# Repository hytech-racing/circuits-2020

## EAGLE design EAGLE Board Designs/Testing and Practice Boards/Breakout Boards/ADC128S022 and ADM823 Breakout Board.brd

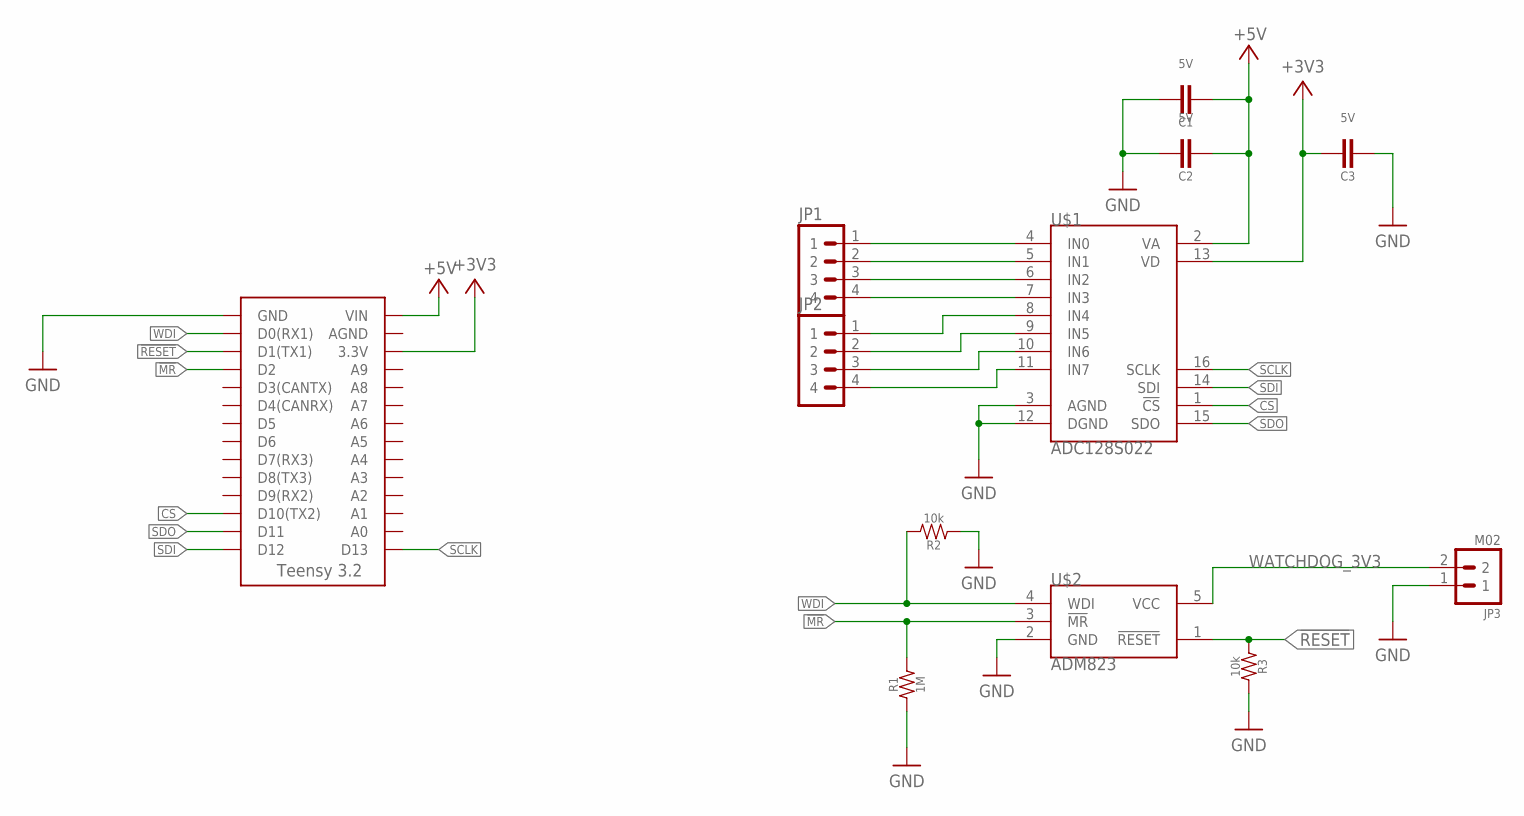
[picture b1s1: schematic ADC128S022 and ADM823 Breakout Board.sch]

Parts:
C1: 1uF; 0603-CAP
C2, C3: 0.1uF; 0603-CAP
JP1, JP2: M04; 1X04
JP3: M02; 1X02
R1: 1M; 0603-RES
R2, R3: 10k; 0603-RES
U$1: ADC128S022; TSSOP-16
U$2: ADM823; SOT323-5
U$3: TEENSY_3.2_SIMPLE

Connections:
!MR!: R1.2, U$2.3 (!MR!), U$3.D2
!RESET!: R3.1, U$2.1 (!RESET!), U$3.D1(TX1)
+3V3: C3.1, U$1.13 (VD), U$3.3.3V
+5V: C1.2, C2.2, U$1.2 (VA), U$3.VIN
CS: U$1.1 (!CS!), U$3.D10(TX2)
GND: C1.1, C2.1, C3.2, JP3.1, R1.1, R2.1, R3.2, U$1.3 (AGND), U$1.12 (DGND), U$2.2 (GND), U$3.GND
unnamed: JP1.1, U$1.4 (IN0)
unnamed: JP1.2, U$1.5 (IN1)
unnamed: JP1.3, U$1.6 (IN2)
unnamed: JP1.4, U$1.7 (IN3)
unnamed: JP2.1, U$1.8 (IN4)
unnamed: JP2.2, U$1.9 (IN5)
unnamed: JP2.3, U$1.10 (IN6)
unnamed: JP2.4, U$1.11 (IN7)
SCLK: U$1.16 (SCLK), U$3.D13
SDI: U$1.14 (SDI), U$3.D12
SDO: U$1.15 (SDO), U$3.D11
WATCHDOG_3V3: JP3.2, U$2.5 (VCC)
WDI: R2.2, U$2.4 (WDI), U$3.D0(RX1)

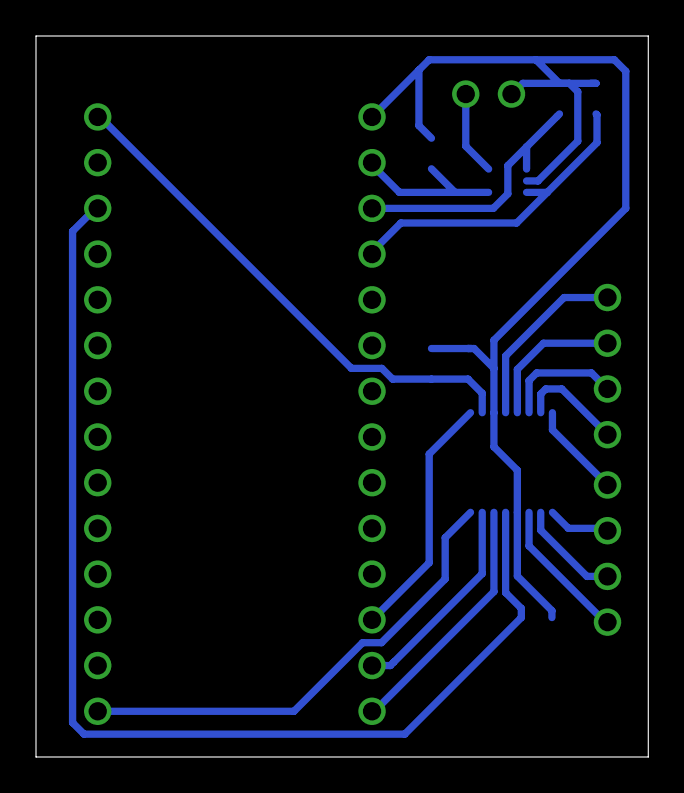
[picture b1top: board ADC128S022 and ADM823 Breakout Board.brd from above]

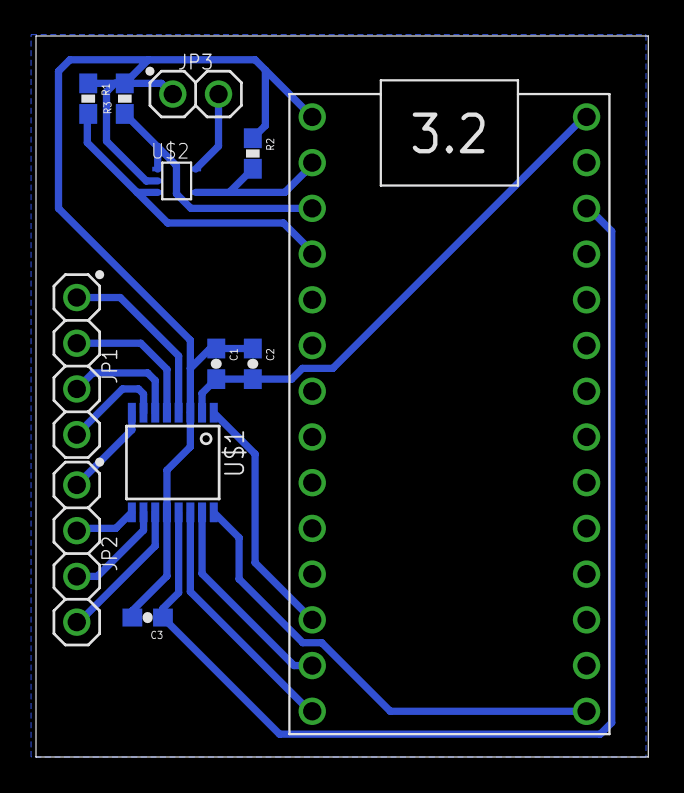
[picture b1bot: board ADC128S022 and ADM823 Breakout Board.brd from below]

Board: 1 copper layer, 34.0 x 40.1 mm, 12 parts (12 on the bottom side), 19 nets.

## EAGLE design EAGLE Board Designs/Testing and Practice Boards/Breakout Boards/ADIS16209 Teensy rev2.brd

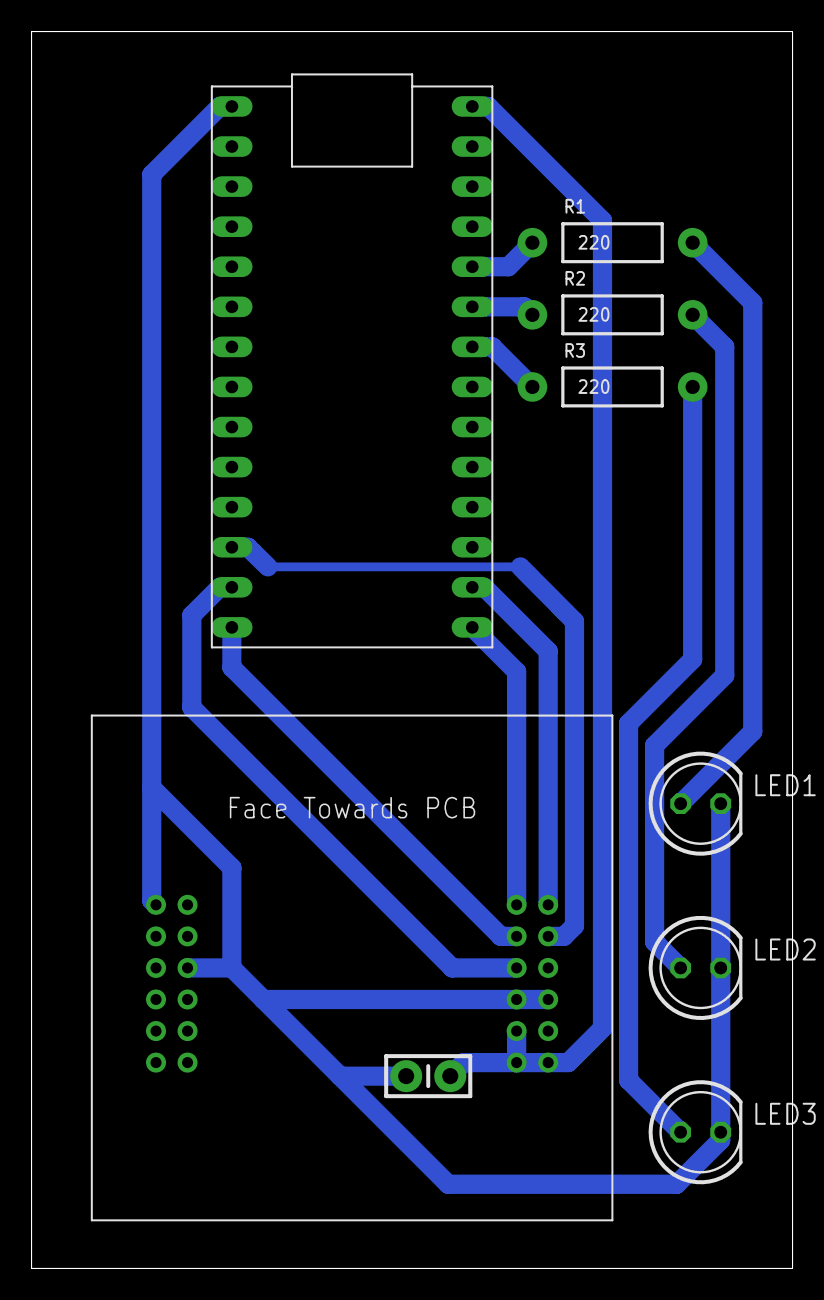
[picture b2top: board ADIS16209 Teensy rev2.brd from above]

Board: 2 copper layers, 48.2 x 78.4 mm, 9 parts (0 on the bottom side), 13 nets.

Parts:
C1: 1uF; CAP-PTH-SMALL-KIT
LED1, LED2, LED3: LED-5MM
R1, R2, R3: 220; AXIAL-0.4
U$1: ADIS16209/PCB
U$2: TEENSY_3.2_SIMPLE

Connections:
+3V3: C1.2, U$1.P$10, U$1.P$11, U$1.P$12, U$2.VIN
CS: U$1.P$3, U$2.D10(TX2)
GND: C1.1, LED1.K, LED2.K, LED3.K, U$1.P$7, U$1.P$8, U$1.P$14, U$1.P$17, U$2.GND
MISO: U$1.P$4, U$2.D12
MOSI: U$1.P$6, U$2.D11
unnamed: LED1.A, R1.P$2
unnamed: U$1.P$1, U$2.A0
unnamed: R1.P$1, U$2.A8
unnamed: R2.P$1, U$2.A7
unnamed: R3.P$1, U$2.A6
unnamed: LED2.A, R2.P$2
unnamed: LED3.A, R3.P$2
SCK: U$1.P$2, U$2.D13

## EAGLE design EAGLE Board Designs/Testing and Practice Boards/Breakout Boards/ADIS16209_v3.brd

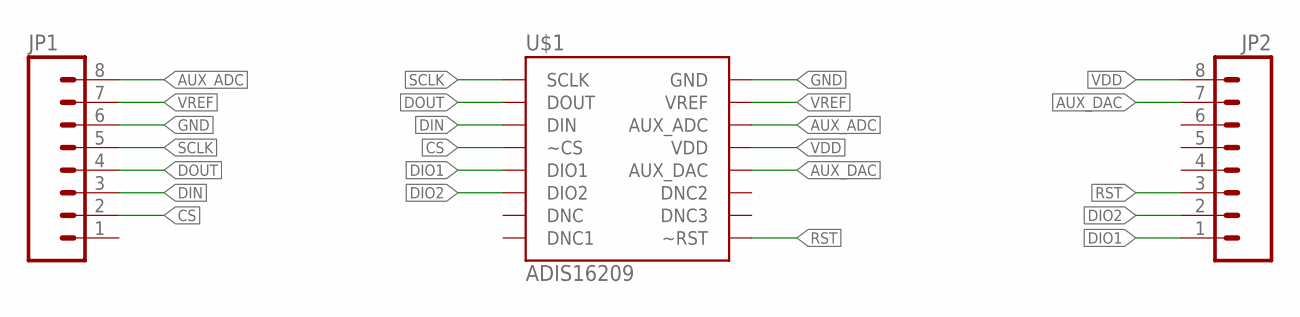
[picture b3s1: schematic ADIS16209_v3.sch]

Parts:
JP1, JP2: M08; 1X08
U$1: ADIS16209; CC-16-2

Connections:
AUX_ADC: JP1.8, U$1.P$14 (AUX_ADC)
AUX_DAC: JP2.7, U$1.P$12 (AUX_DAC)
CS: JP1.2, U$1.P$4 (~CS)
DIN: JP1.3, U$1.P$3 (DIN)
DIO1: JP2.1, U$1.P$5 (DIO1)
DIO2: JP2.2, U$1.P$6 (DIO2)
DOUT: JP1.4, U$1.P$2 (DOUT)
GND: JP1.6, U$1.P$16 (GND)
RST: JP2.3, U$1.P$9 (~RST)
SCLK: JP1.5, U$1.P$1 (SCLK)
VDD: JP2.8, U$1.P$13 (VDD)
VREF: JP1.7, U$1.P$15 (VREF)

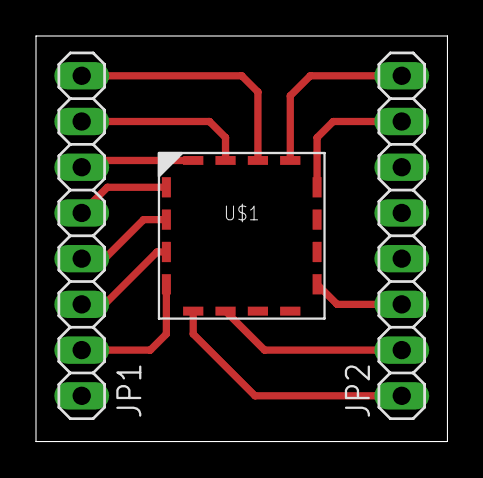
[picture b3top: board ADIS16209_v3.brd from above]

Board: 2 copper layers, 22.9 x 22.5 mm, 3 parts (0 on the bottom side), 12 nets.

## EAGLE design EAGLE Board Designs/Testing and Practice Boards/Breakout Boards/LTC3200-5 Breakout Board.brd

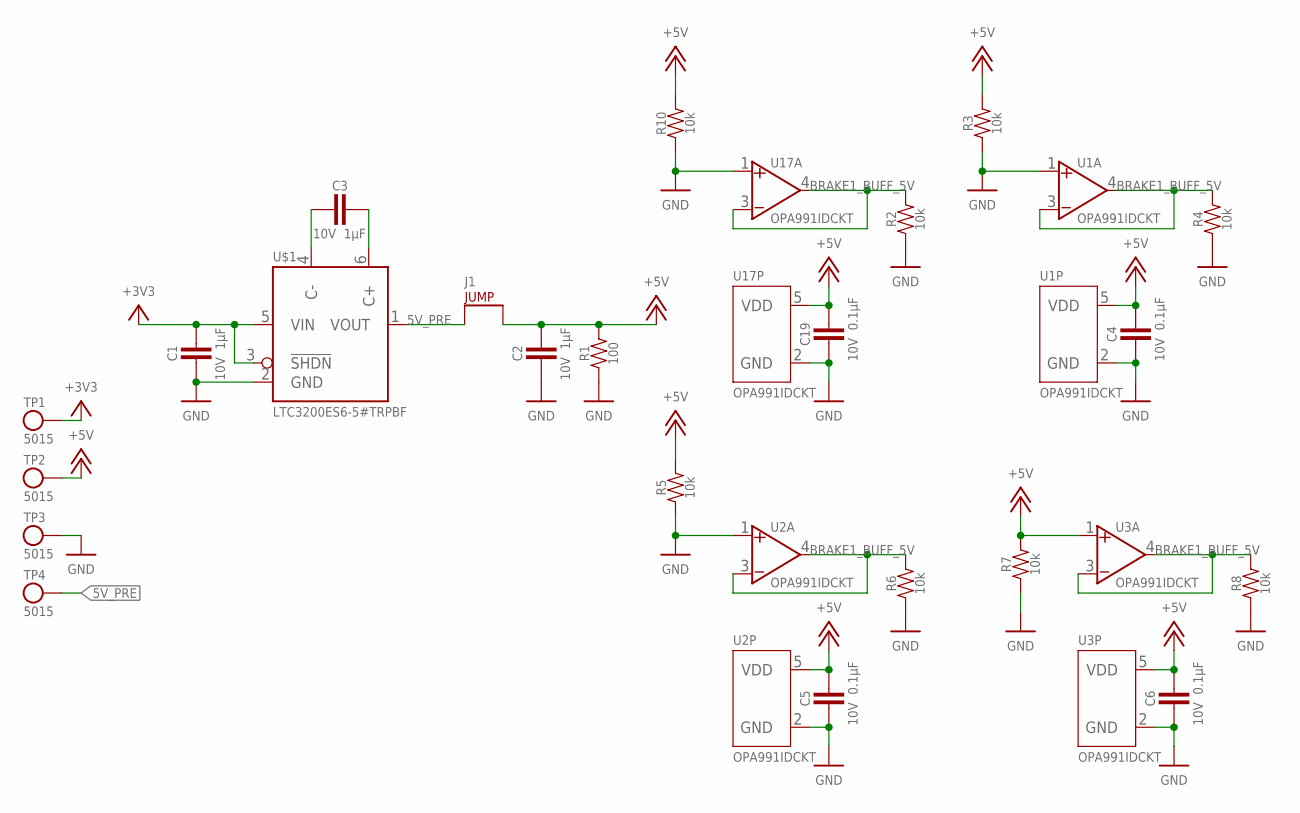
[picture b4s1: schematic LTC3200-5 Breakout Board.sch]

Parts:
C1, C2, C3: CAPACITOR_0603_10V_1UF; 0603-CAP
C4, C5, C6, C19: CAPACITOR_0603_10V_0.1UF; 0603-CAP
J1: JUMPER_1X02_; 1X02
R1: RESISTOR_0603_100; 0603-RES
R2, R3, R4, R5, R6, R7, R8, R10: RESISTOR_0603_10K; 0603-RES
TP1, TP2, TP3, TP4: TEST_POINT; MICRO_MINIATURE
U1, U2, U3, U17: OPAMP_1_CHANNEL_OPA991; SC-70-5
U$1: LTC3200-5; SOT-23-6

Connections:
5V_PRE: J1.1, TP4.1, U$1.1 (VOUT)
+3V3: C1.1, TP1.1, U$1.3 (!SHDN), U$1.5 (VIN)
+5V: C2.1, C4.1, C5.1, C6.1, C19.1, J1.2, R1.2, R3.2, R5.2, R7.2, R10.2, TP2.1, U1.5 (VDD), U2.5 (VDD), U3.1 (VIN+), U3.5 (VDD), U17.5 (VDD)
BRAKE1_BUFF_5V: R2.2, R4.2, R6.2, R8.2, U1.3 (VIN-), U1.4 (VOUT), U2.3 (VIN-), U2.4 (VOUT), U3.3 (VIN-), U3.4 (VOUT), U17.3 (VIN-), U17.4 (VOUT)
GND: C1.2, C2.2, C4.2, C5.2, C6.2, C19.2, R1.1, R2.1, R3.1, R4.1, R5.1, R6.1, R7.1, R8.1, R10.1, TP3.1, U1.1 (VIN+), U1.2 (GND), U2.1 (VIN+), U2.2 (GND), U3.2 (GND), U17.1 (VIN+), U17.2 (GND), U$1.2 (GND)
unnamed: C3.2, U$1.4 (C-)
unnamed: C3.1, U$1.6 (C+)

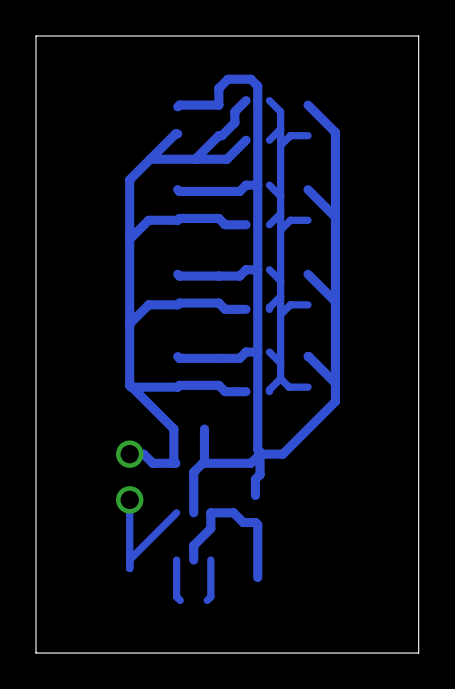
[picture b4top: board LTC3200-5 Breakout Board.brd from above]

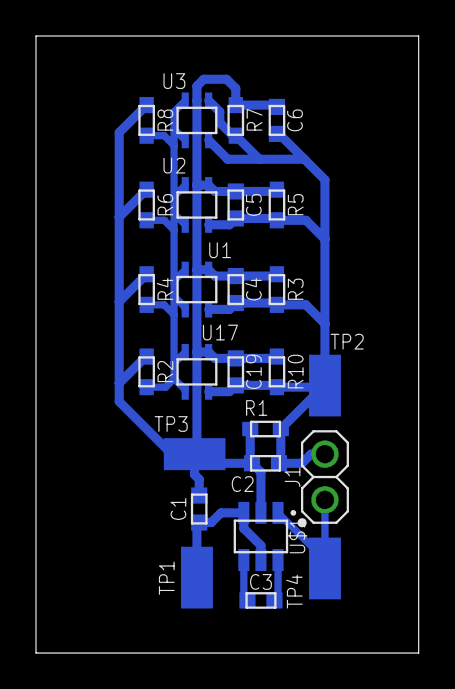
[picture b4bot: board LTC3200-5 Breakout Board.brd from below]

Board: 1 copper layer, 21.3 x 34.3 mm, 26 parts (26 on the bottom side), 7 nets.

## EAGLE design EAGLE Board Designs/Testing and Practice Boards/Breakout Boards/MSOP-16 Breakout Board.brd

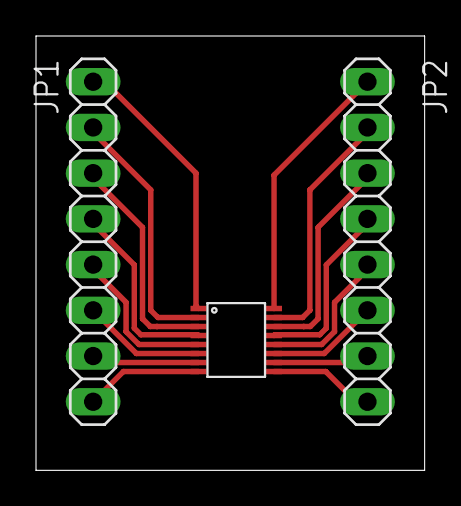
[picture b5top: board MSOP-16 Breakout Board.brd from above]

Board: 2 copper layers, 21.6 x 24.1 mm, 3 parts (0 on the bottom side), 15 nets.

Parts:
JP1, JP2: 1X08
U$1: LTC6820; MSOP-16

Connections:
unnamed: JP1.8, U$1.8
unnamed: JP1.6, U$1.6
unnamed: JP1.5, U$1.5
unnamed: JP1.4, U$1.4
unnamed: JP1.3, U$1.3
unnamed: JP1.1, U$1.1
unnamed: JP1.2, JP1.7, U$1.2, U$1.7
unnamed: JP2.8, U$1.9
unnamed: JP2.7, U$1.10
unnamed: JP2.6, U$1.11
unnamed: JP2.5, U$1.12
unnamed: JP2.4, U$1.13
unnamed: JP2.3, U$1.14
unnamed: JP2.2, U$1.15
unnamed: JP2.1, U$1.16

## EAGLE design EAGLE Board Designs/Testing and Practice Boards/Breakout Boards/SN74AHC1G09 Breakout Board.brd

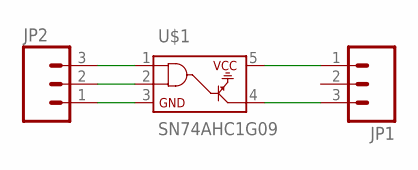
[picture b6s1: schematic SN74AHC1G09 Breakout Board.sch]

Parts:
JP1, JP2: M03; 1X03
U$1: SN74AHC1G09; SOT-23-5

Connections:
unnamed: JP2.3, U$1.1
unnamed: JP2.2, U$1.2
unnamed: JP2.1, U$1.3
unnamed: JP1.1, U$1.5
unnamed: JP1.3, U$1.4

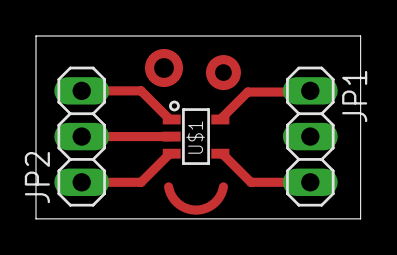
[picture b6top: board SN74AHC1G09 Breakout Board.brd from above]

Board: 2 copper layers, 18.0 x 10.2 mm, 3 parts (0 on the bottom side), 5 nets.

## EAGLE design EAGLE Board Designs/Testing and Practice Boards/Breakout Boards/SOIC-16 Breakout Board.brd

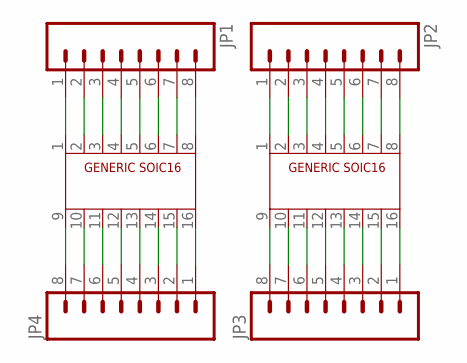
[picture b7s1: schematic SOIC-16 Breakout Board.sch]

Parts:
JP1, JP2, JP3, JP4: M08; 1X08
U$1, U$2: SOIC16; SOIC-16

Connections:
unnamed: JP1.1, U$1.1
unnamed: JP1.2, U$1.2
unnamed: JP1.3, U$1.3
unnamed: JP1.4, U$1.4
unnamed: JP1.5, U$1.5
unnamed: JP1.6, U$1.6
unnamed: JP1.7, U$1.7
unnamed: JP1.8, U$1.8
unnamed: JP2.1, U$2.1
unnamed: JP2.2, U$2.2
unnamed: JP2.3, U$2.3
unnamed: JP2.4, U$2.4
unnamed: JP2.5, U$2.5
unnamed: JP2.6, U$2.6
unnamed: JP2.7, U$2.7
unnamed: JP2.8, U$2.8
unnamed: JP3.1, U$2.16
unnamed: JP3.2, U$2.15
unnamed: JP3.3, U$2.14
unnamed: JP3.4, U$2.13
unnamed: JP3.5, U$2.12
unnamed: JP3.6, U$2.11
unnamed: JP3.7, U$2.10
unnamed: JP3.8, U$2.9
unnamed: JP4.1, U$1.16
unnamed: JP4.2, U$1.15
unnamed: JP4.3, U$1.14
unnamed: JP4.4, U$1.13
unnamed: JP4.5, U$1.12
unnamed: JP4.6, U$1.11
unnamed: JP4.7, U$1.10
unnamed: JP4.8, U$1.9

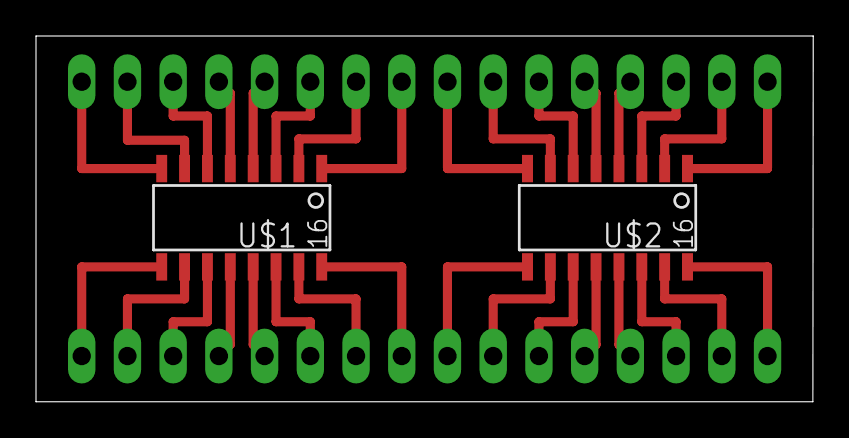
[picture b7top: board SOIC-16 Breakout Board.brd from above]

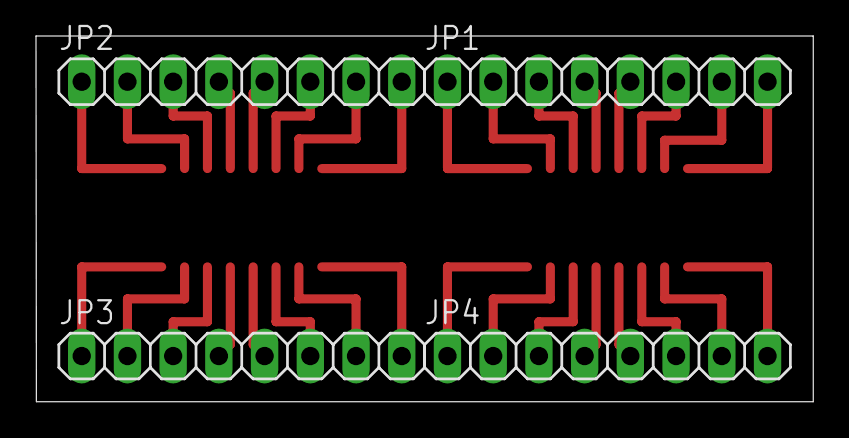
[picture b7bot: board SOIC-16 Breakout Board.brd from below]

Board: 2 copper layers, 43.2 x 20.3 mm, 6 parts (4 on the bottom side), 32 nets.

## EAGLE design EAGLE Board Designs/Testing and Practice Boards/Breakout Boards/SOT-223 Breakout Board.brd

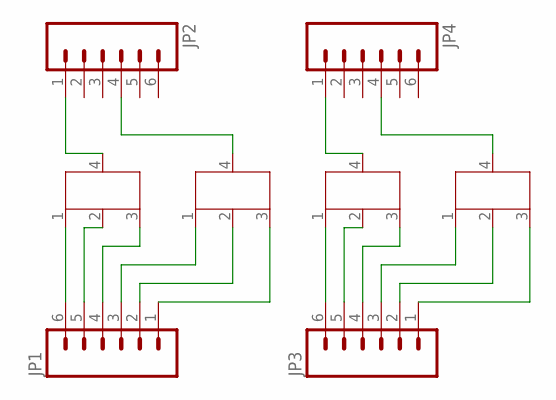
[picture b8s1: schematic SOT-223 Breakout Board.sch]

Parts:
JP1, JP2, JP3, JP4: M06; 1X06
U$1, U$2, U$3, U$4: SOT223

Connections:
unnamed: JP2.1, U$1.4
unnamed: JP1.6, U$1.1
unnamed: JP1.5, U$1.2
unnamed: JP1.4, U$1.3
unnamed: JP1.3, U$3.1
unnamed: JP1.2, U$3.2
unnamed: JP1.1, U$3.3
unnamed: JP2.4, U$3.4
unnamed: JP4.1, U$2.4
unnamed: JP4.4, U$4.4
unnamed: JP3.6, U$2.1
unnamed: JP3.5, U$2.2
unnamed: JP3.4, U$2.3
unnamed: JP3.3, U$4.1
unnamed: JP3.2, U$4.2
unnamed: JP3.1, U$4.3

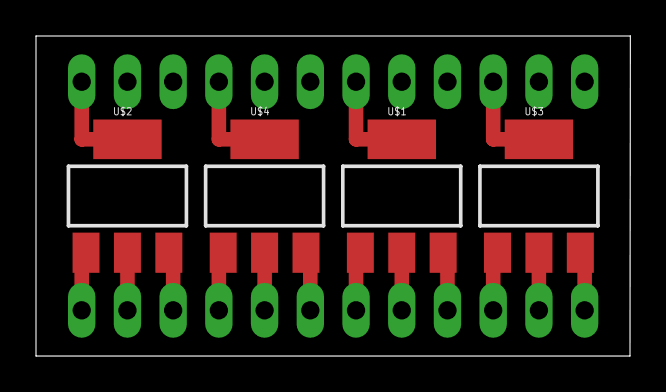
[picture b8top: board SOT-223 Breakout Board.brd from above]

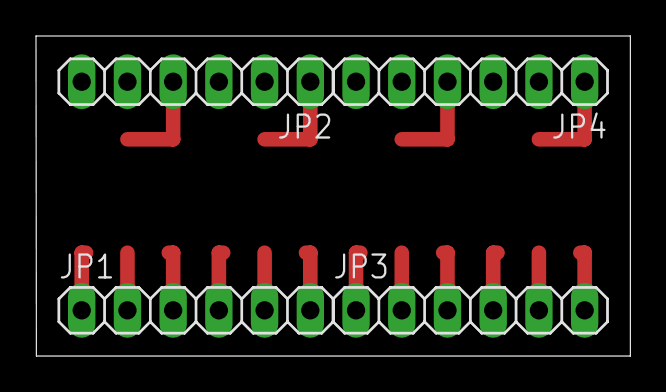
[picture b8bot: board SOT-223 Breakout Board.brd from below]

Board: 2 copper layers, 33.0 x 17.8 mm, 8 parts (4 on the bottom side), 16 nets.
